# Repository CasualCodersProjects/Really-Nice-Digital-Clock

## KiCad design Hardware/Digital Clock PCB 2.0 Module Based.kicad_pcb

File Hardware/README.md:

# Digital Clock Hardware

## Notice:
There is a hardware change between the 8 clocks sold on Tindie and these. The original production clocks from tindie are:  
- Missing a copper trace between the 3v3 line and the 3v3 output of the LDO. This is corrected with a hand-assembled solder bridge.  
- The I2C lines are shifted right by one pin. The Tindie version uses GPIO 21 for SDA and GPIO 33 for SCL.  
- The Tindie clocks have a manually soldered bodge to move one of the binary coded digits off GPIO 46, which is an input only strapping pin.

## Description
This is an internet connected Clock which synchronizes with NTP servers to perpetually serve an accurate time. It is unable to keep very good time by itself. As such, it requires a stable, consistent network connection to show reliable time. With that, it should always be accurate within a second or so. To improve accuracy, you could modify the firmware to check every hour or half hour instead of once per day.  

It's built using BCD Decoders and 1.5" Seven segment displays for a nice clean look. It also utilizes an ambient light sensor to automatically brighten and dim to match the room light.  

This clock serves it's own webpage for configuration. Upon first boot, it activates an access point ssid `NiceClock`, password `MinesBigger`. Connect to the default gateway `192.168.4.1` to configure the clock and provide network credentials. Once credentials are provided, it should instantly connect and acquire the network time.  
To view the device's IP address, press the boot button on the rear.

## Hacking
This device openly exposes both a TTL UART and JTAG port on the rear of te board, near the ESP Module. You can also use the USB Port to program and upload code. While holding the boot button, then press reset. This enters the ESP32 into bootloader mode, and allows you to re-flash new firmware or filesystem to the device.

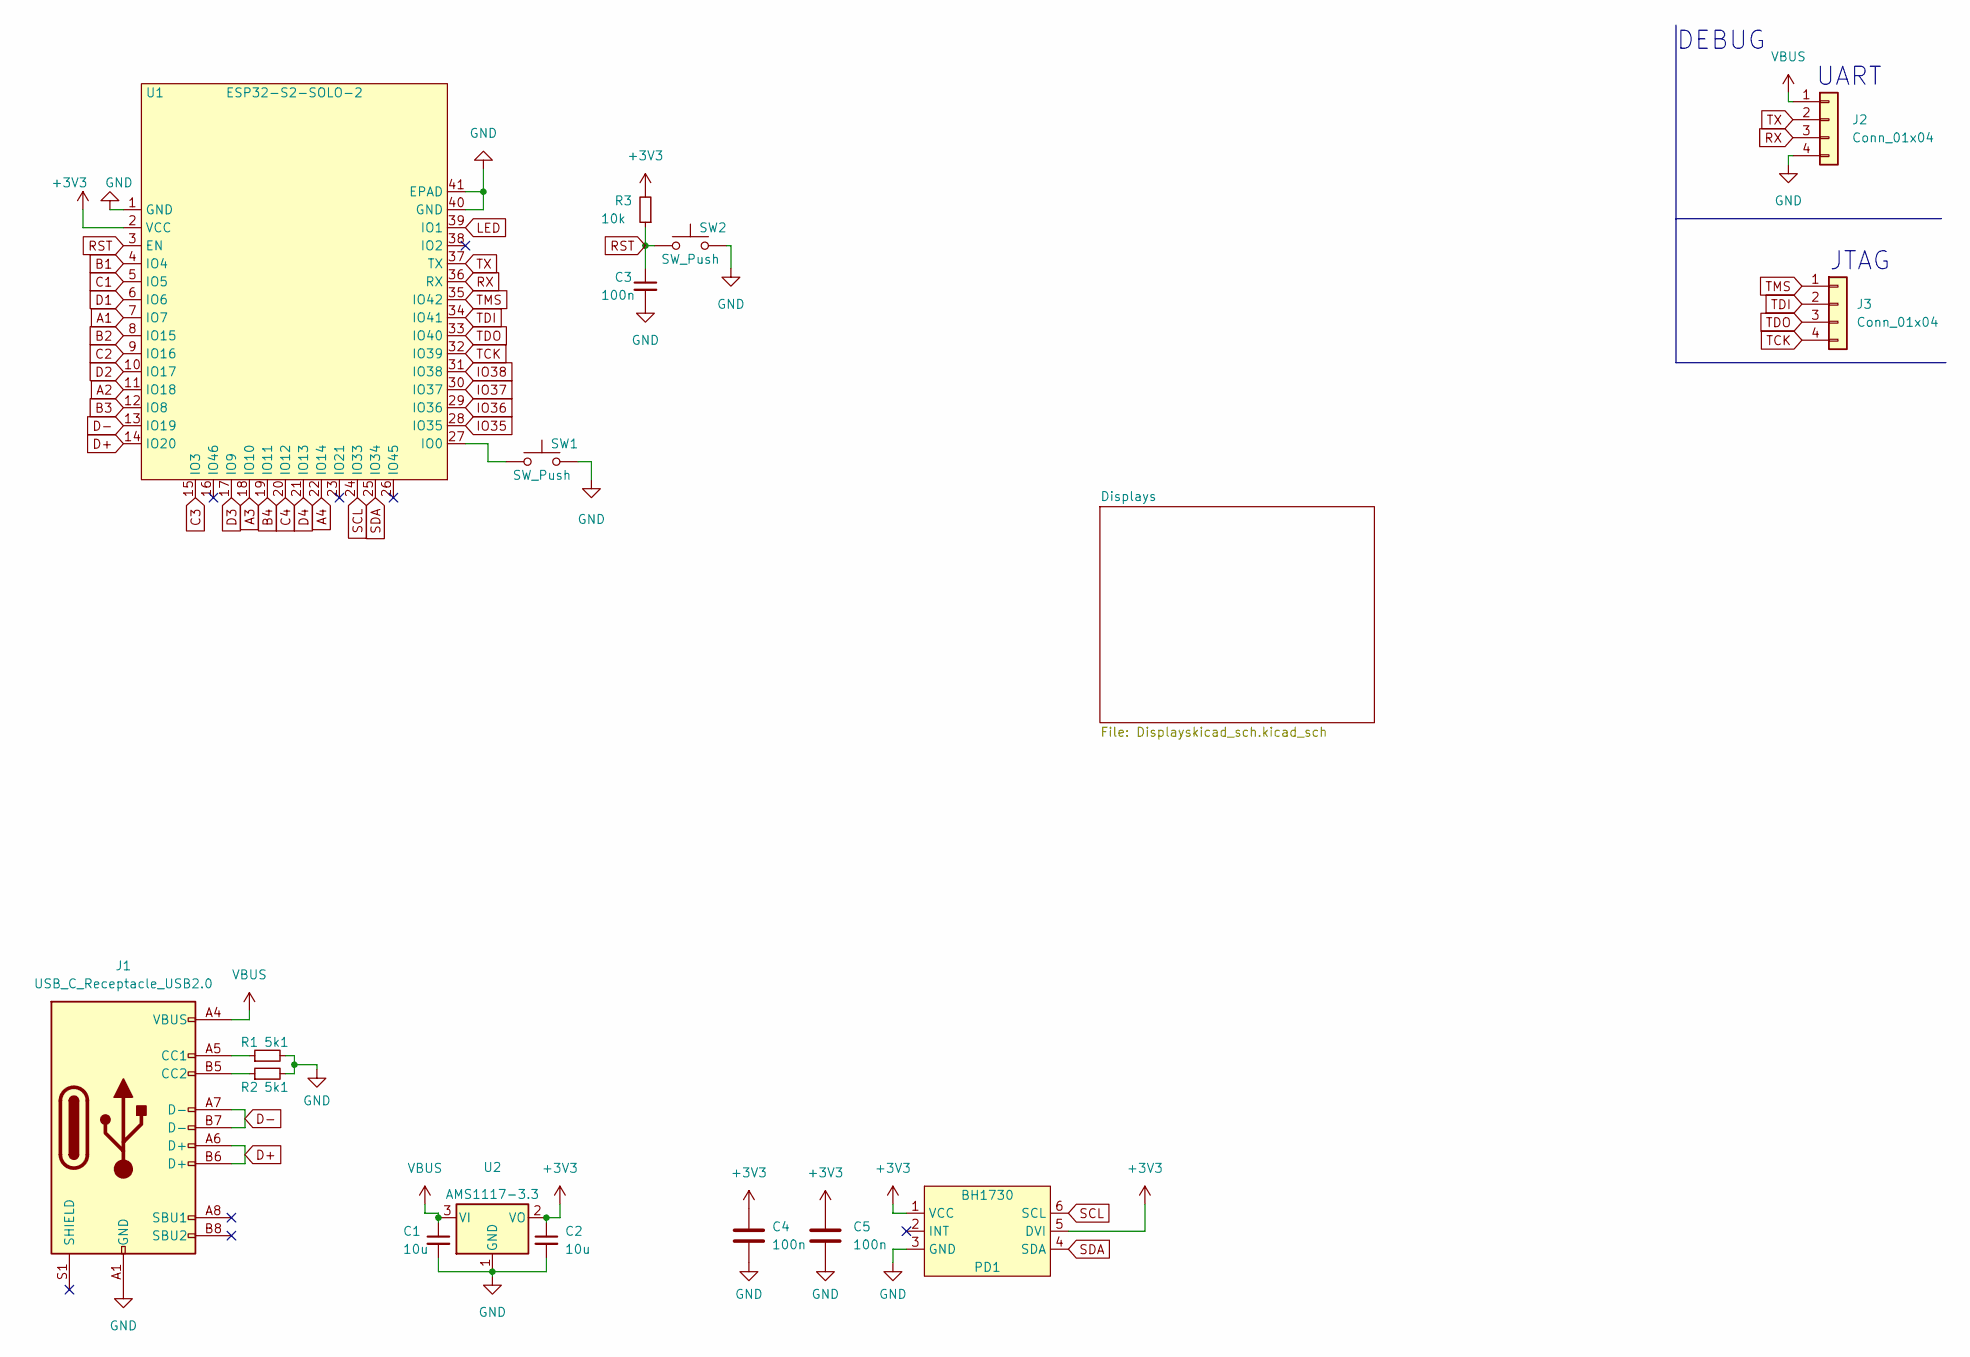
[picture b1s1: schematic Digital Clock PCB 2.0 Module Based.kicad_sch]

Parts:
C1, C2: 10u; C_0805_2012Metric
C3, C4, C5: 100n; C_0603_1608Metric
J1: USB_C_Receptacle_USB2.0; USB_C_Receptacle_HRO_TYPE-C-31-M-12
J2, J3: Conn_01x04; PinHeader_1x04_P2.54mm_Vertical
PD1: BH1730; WSOF6
R1, R2: 5k1; R_0603_1608Metric
R3: 10k; R_0603_1608Metric
SW1, SW2: SW_Push; 5.2mm_Tactile_Push_Button
U1: ESP32-S2-SOLO-2; ESP32-S3-WROOM-1
U2: AMS1117-3.3; SOT-223-3_TabPin2

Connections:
+3V3: C2.1, C4.1, C5.1, PD1.1 (VCC), PD1.5 (DVI), R3.2, U1.2 (VCC), U2.2 (VO); also elsewhere on the board
A1: U1.7 (IO7); also elsewhere on the board
A2: U1.11 (IO18); also elsewhere on the board
A3: U1.18 (IO10); also elsewhere on the board
A4: U1.22 (IO14); also elsewhere on the board
B1: U1.4 (IO4); also elsewhere on the board
B2: U1.8 (IO15); also elsewhere on the board
B3: U1.12 (IO8); also elsewhere on the board
B4: U1.19 (IO11); also elsewhere on the board
C1: U1.5 (IO5); also elsewhere on the board
C2: U1.9 (IO16); also elsewhere on the board
C3: U1.15 (IO3); also elsewhere on the board
C4: U1.20 (IO12); also elsewhere on the board
D1: U1.6 (IO6); also elsewhere on the board
D2: U1.10 (IO17); also elsewhere on the board
D3: U1.17 (IO9); also elsewhere on the board
D4: U1.21 (IO13); also elsewhere on the board
D+: J1.A6 (D+), J1.B6 (D+), U1.14 (IO20)
D-: J1.A7 (D-), J1.B7 (D-), U1.13 (IO19)
GND: C1.2, C2.2, C3.2, C4.2, C5.2, J1.A1 (GND), J1.A12 (GND), J1.B1 (GND), J1.B12 (GND), J2.4, PD1.3 (GND), R1.2, R2.2, SW1.2, SW2.2, U1.1 (GND), U1.40 (GND), U1.41 (EPAD), U2.1 (GND); also elsewhere on the board
IO35: U1.28 (IO35); also elsewhere on the board
IO36: U1.29 (IO36); also elsewhere on the board
IO37: U1.30 (IO37); also elsewhere on the board
IO38: U1.31 (IO38); also elsewhere on the board
LED: U1.39 (IO1); also elsewhere on the board
unnamed: J1.A5 (CC1), R1.1
unnamed: J1.B5 (CC2), R2.1
unnamed: SW1.1, U1.27 (IO0)
RST: C3.1, R3.1, SW2.1, U1.3 (EN)
RX: J2.3, U1.36 (RX)
SCL: PD1.6 (SCL), U1.24 (IO33)
SDA: PD1.4 (SDA), U1.25 (IO34)
TCK: J3.4, U1.32 (IO39)
TDI: J3.2, U1.34 (IO41)
TDO: J3.3, U1.33 (IO40)
TMS: J3.1, U1.35 (IO42)
TX: J2.2, U1.37 (TX)
VBUS: C1.1, J1.A4 (VBUS), J1.A9 (VBUS), J1.B4 (VBUS), J1.B9 (VBUS), J2.1, U2.3 (VI); also elsewhere on the board

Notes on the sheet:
DEBUG
UART
JTAG

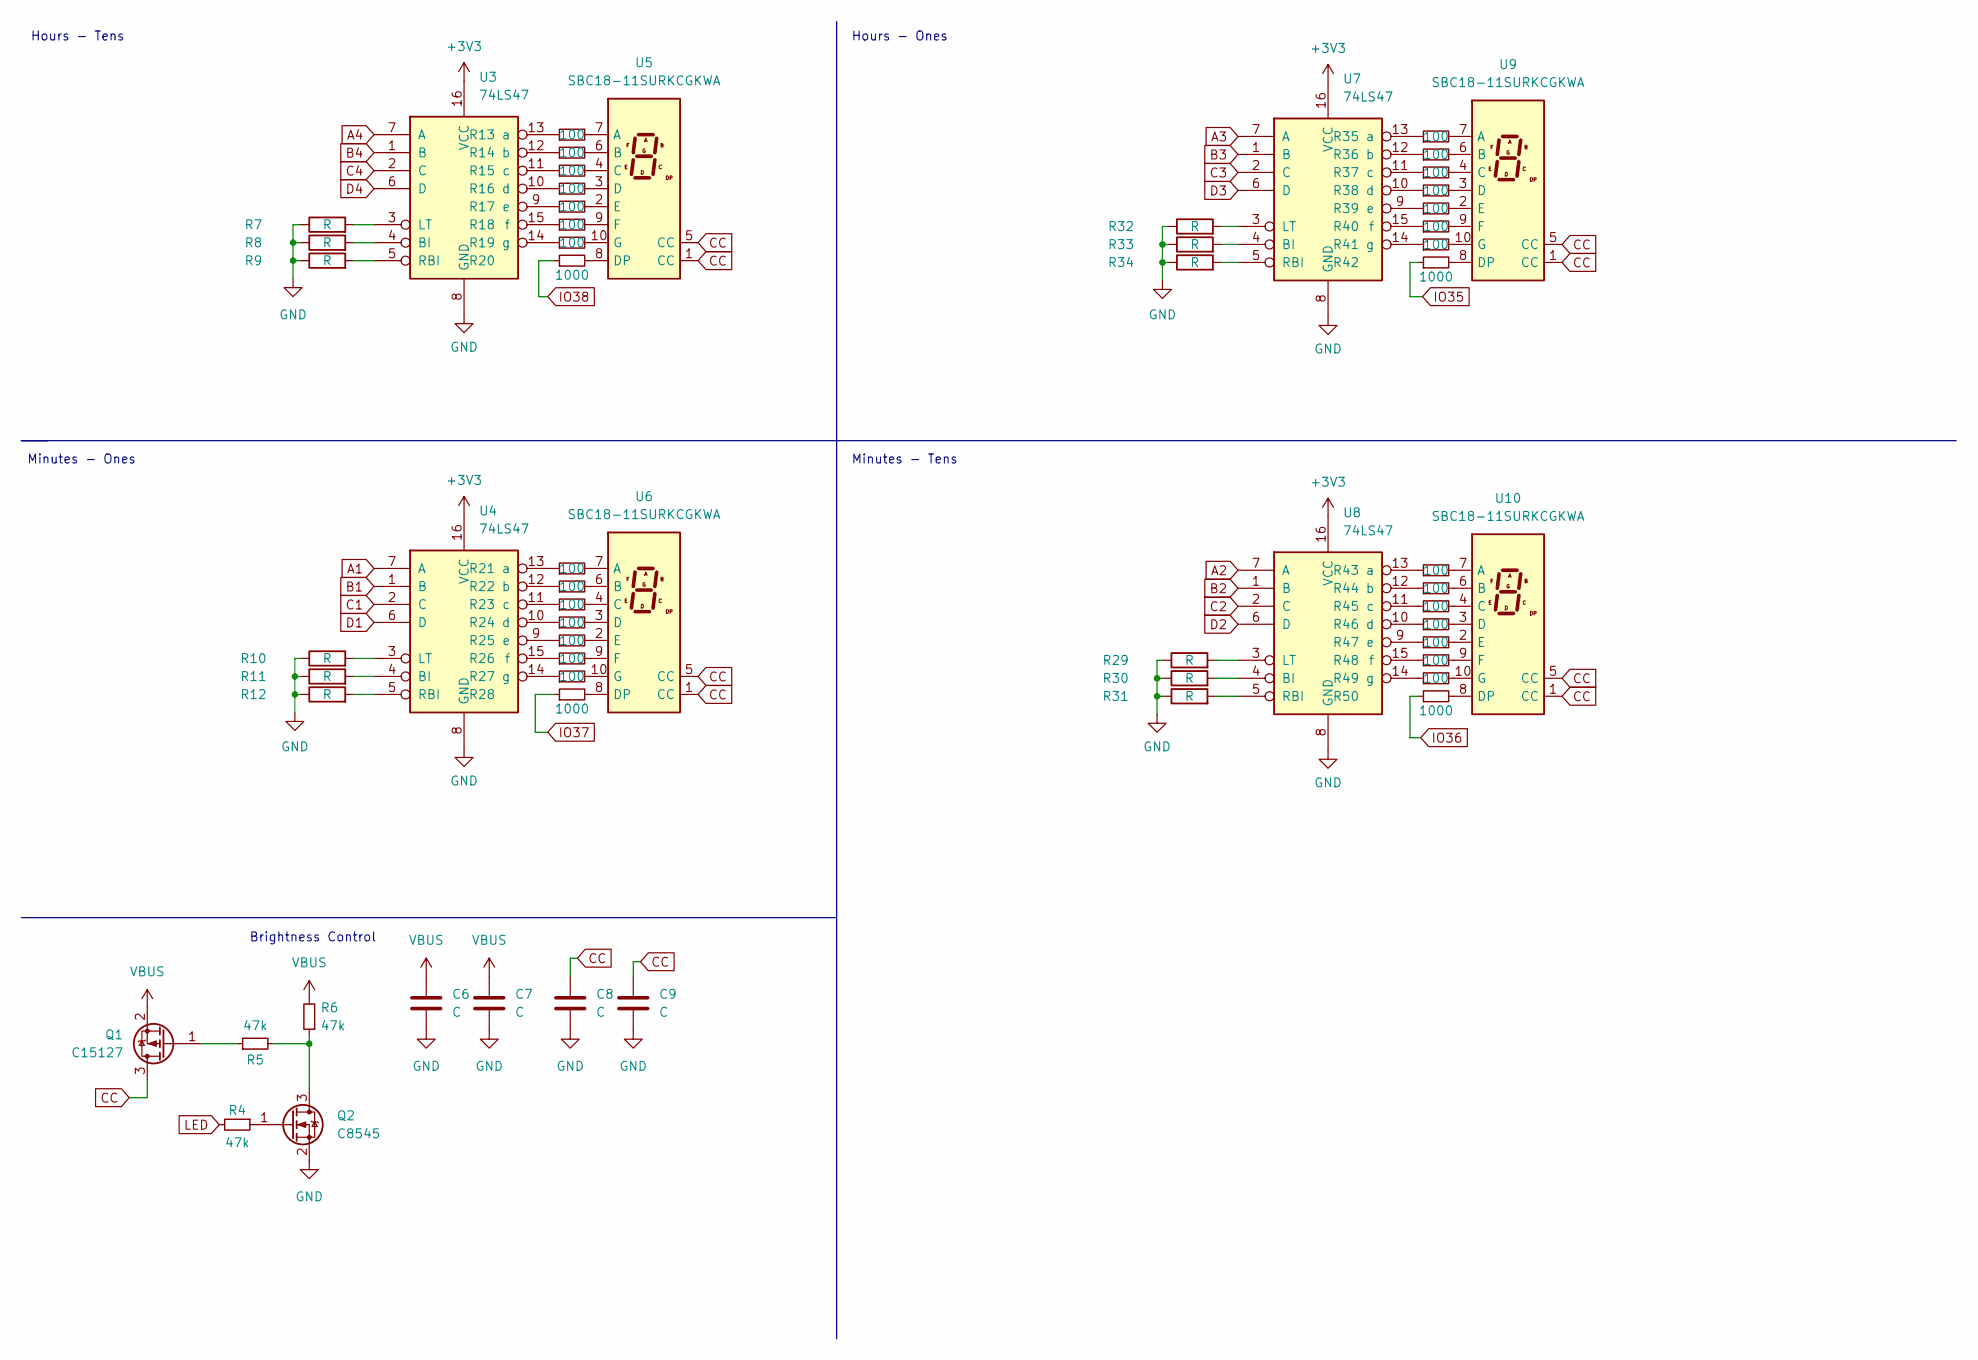
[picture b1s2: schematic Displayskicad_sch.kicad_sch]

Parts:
C6, C7, C8, C9: C; C_0805_2012Metric
Q1: C15127; SOT-23
Q2: C8545; SOT-23
R4, R5, R6: 47k; R_0805_2012Metric
R7, R8, R9, R10, R11, R12, R29, R30, R31, R32, R33, R34: R; R_0603_1608Metric
R13, R14, R15, R16, R17, R18, R19, R21, R22, R23, R24, R25, R26, R27, R35, R36, R37, R38, R39, R40, R41, R43, R44, R45, R46, R47, R48, R49: 100; R_0805_2012Metric
R20, R28, R42, R50: 1000; R_0805_2012Metric
U3, U4, U7, U8: 74LS47; SOIC-16_4.55x10.3mm_P1.27mm
U5, U6, U9, U10: SBC18-11SURKCGKWA; Segment_Display_1-5_inch

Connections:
+3V3: U3.16 (VCC), U4.16 (VCC), U7.16 (VCC), U8.16 (VCC); also elsewhere on the board
A1: U4.7 (A); also elsewhere on the board
A2: U8.7 (A); also elsewhere on the board
A3: U7.7 (A); also elsewhere on the board
A4: U3.7 (A); also elsewhere on the board
B1: U4.1 (B); also elsewhere on the board
B2: U8.1 (B); also elsewhere on the board
B3: U7.1 (B); also elsewhere on the board
B4: U3.1 (B); also elsewhere on the board
C1: U4.2 (C); also elsewhere on the board
C2: U8.2 (C); also elsewhere on the board
C3: U7.2 (C); also elsewhere on the board
C4: U3.2 (C); also elsewhere on the board
CC: C8.1, C9.1, Q1.3 (D), U5.1 (CC), U5.5 (CC), U6.1 (CC), U6.5 (CC), U9.1 (CC), U9.5 (CC), U10.1 (CC), U10.5 (CC)
D1: U4.6 (D); also elsewhere on the board
D2: U8.6 (D); also elsewhere on the board
D3: U7.6 (D); also elsewhere on the board
D4: U3.6 (D); also elsewhere on the board
GND: C6.2, C7.2, C8.2, C9.2, Q2.2 (S), R7.1, R8.1, R9.1, R10.1, R11.1, R12.1, R29.1, R30.1, R31.1, R32.1, R33.1, R34.1, U3.8 (GND), U4.8 (GND), U7.8 (GND), U8.8 (GND); also elsewhere on the board
IO35: R42.1; also elsewhere on the board
IO36: R50.1; also elsewhere on the board
IO37: R28.1; also elsewhere on the board
IO38: R20.1; also elsewhere on the board
LED: R4.2; also elsewhere on the board
unnamed: Q1.1 (G), R5.1
unnamed: Q2.3 (D), R5.2, R6.1
unnamed: Q2.1 (G), R4.1
unnamed: R8.2, U3.4 (BI)
unnamed: R7.2, U3.3 (LT)
unnamed: R9.2, U3.5 (RBI)
unnamed: R13.1, U3.13 (a)
unnamed: R14.1, U3.12 (b)
unnamed: R15.1, U3.11 (c)
unnamed: R16.1, U3.10 (d)
unnamed: R17.1, U3.9 (e)
unnamed: R18.1, U3.15 (f)
unnamed: R19.1, U3.14 (g)
unnamed: R11.2, U4.4 (BI)
unnamed: R10.2, U4.3 (LT)
unnamed: R12.2, U4.5 (RBI)
unnamed: R21.1, U4.13 (a)
unnamed: R22.1, U4.12 (b)
unnamed: R23.1, U4.11 (c)
unnamed: R24.1, U4.10 (d)
unnamed: R25.1, U4.9 (e)
unnamed: R26.1, U4.15 (f)
unnamed: R27.1, U4.14 (g)
unnamed: R13.2, U5.7 (A)
unnamed: R14.2, U5.6 (B)
unnamed: R15.2, U5.4 (C)
unnamed: R16.2, U5.3 (D)
unnamed: R20.2, U5.8 (DP)
unnamed: R17.2, U5.2 (E)
unnamed: R18.2, U5.9 (F)
unnamed: R19.2, U5.10 (G)
unnamed: R21.2, U6.7 (A)
unnamed: R22.2, U6.6 (B)
unnamed: R23.2, U6.4 (C)
unnamed: R24.2, U6.3 (D)
unnamed: R28.2, U6.8 (DP)
unnamed: R25.2, U6.2 (E)
unnamed: R26.2, U6.9 (F)
unnamed: R27.2, U6.10 (G)
unnamed: R33.2, U7.4 (BI)
unnamed: R32.2, U7.3 (LT)
unnamed: R34.2, U7.5 (RBI)
unnamed: R35.1, U7.13 (a)
unnamed: R36.1, U7.12 (b)
unnamed: R37.1, U7.11 (c)
unnamed: R38.1, U7.10 (d)
unnamed: R39.1, U7.9 (e)
unnamed: R40.1, U7.15 (f)
unnamed: R41.1, U7.14 (g)
unnamed: R30.2, U8.4 (BI)
unnamed: R29.2, U8.3 (LT)
unnamed: R31.2, U8.5 (RBI)
unnamed: R43.1, U8.13 (a)
unnamed: R44.1, U8.12 (b)
unnamed: R45.1, U8.11 (c)
unnamed: R46.1, U8.10 (d)
unnamed: R47.1, U8.9 (e)
unnamed: R48.1, U8.15 (f)
unnamed: R49.1, U8.14 (g)
unnamed: R35.2, U9.7 (A)
unnamed: R36.2, U9.6 (B)
unnamed: R37.2, U9.4 (C)
unnamed: R38.2, U9.3 (D)
unnamed: R42.2, U9.8 (DP)
unnamed: R39.2, U9.2 (E)
unnamed: R40.2, U9.9 (F)
unnamed: R41.2, U9.10 (G)
unnamed: R43.2, U10.7 (A)
unnamed: R44.2, U10.6 (B)
unnamed: R45.2, U10.4 (C)
unnamed: R46.2, U10.3 (D)
unnamed: R50.2, U10.8 (DP)
unnamed: R47.2, U10.2 (E)
unnamed: R48.2, U10.9 (F)
unnamed: R49.2, U10.10 (G)
VBUS: C6.1, C7.1, Q1.2 (S), R6.2; also elsewhere on the board

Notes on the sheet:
Hours - Tens
Hours - Ones
Minutes - Tens
Brightness Control
Minutes - Ones

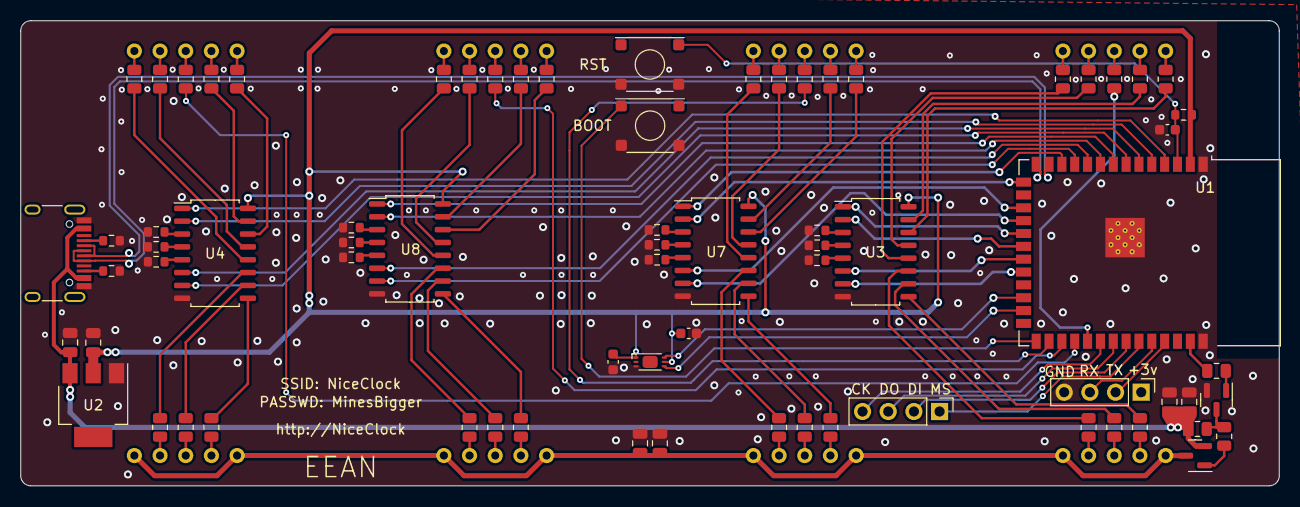
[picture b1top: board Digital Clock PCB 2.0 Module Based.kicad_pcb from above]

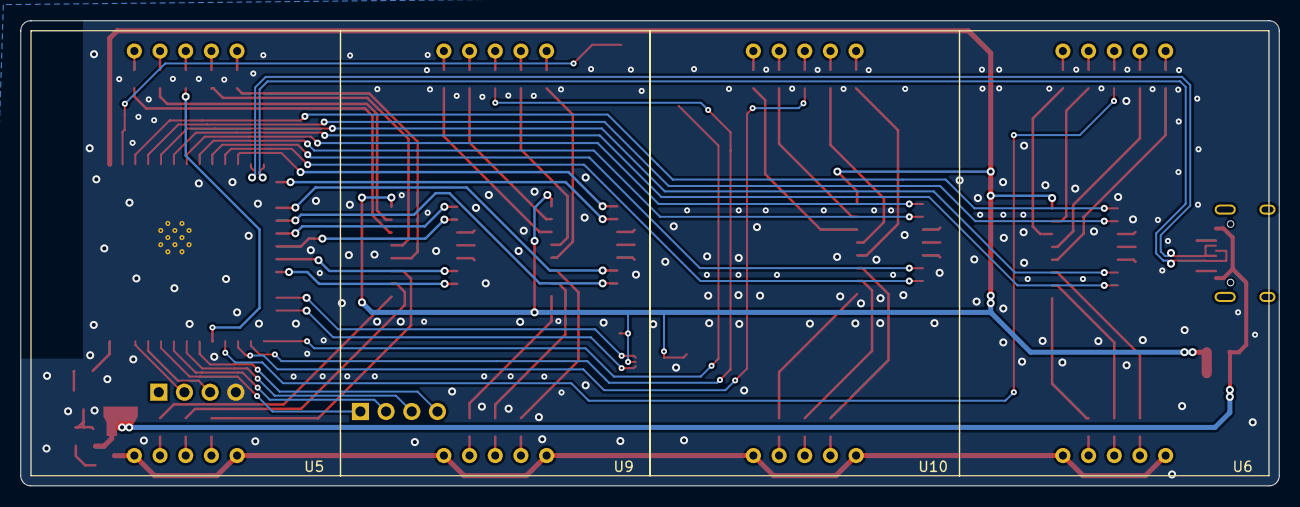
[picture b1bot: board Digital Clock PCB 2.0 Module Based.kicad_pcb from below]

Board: 2 copper layers, 124.5 x 46.0 mm, 77 parts (4 on the bottom side), 114 nets.

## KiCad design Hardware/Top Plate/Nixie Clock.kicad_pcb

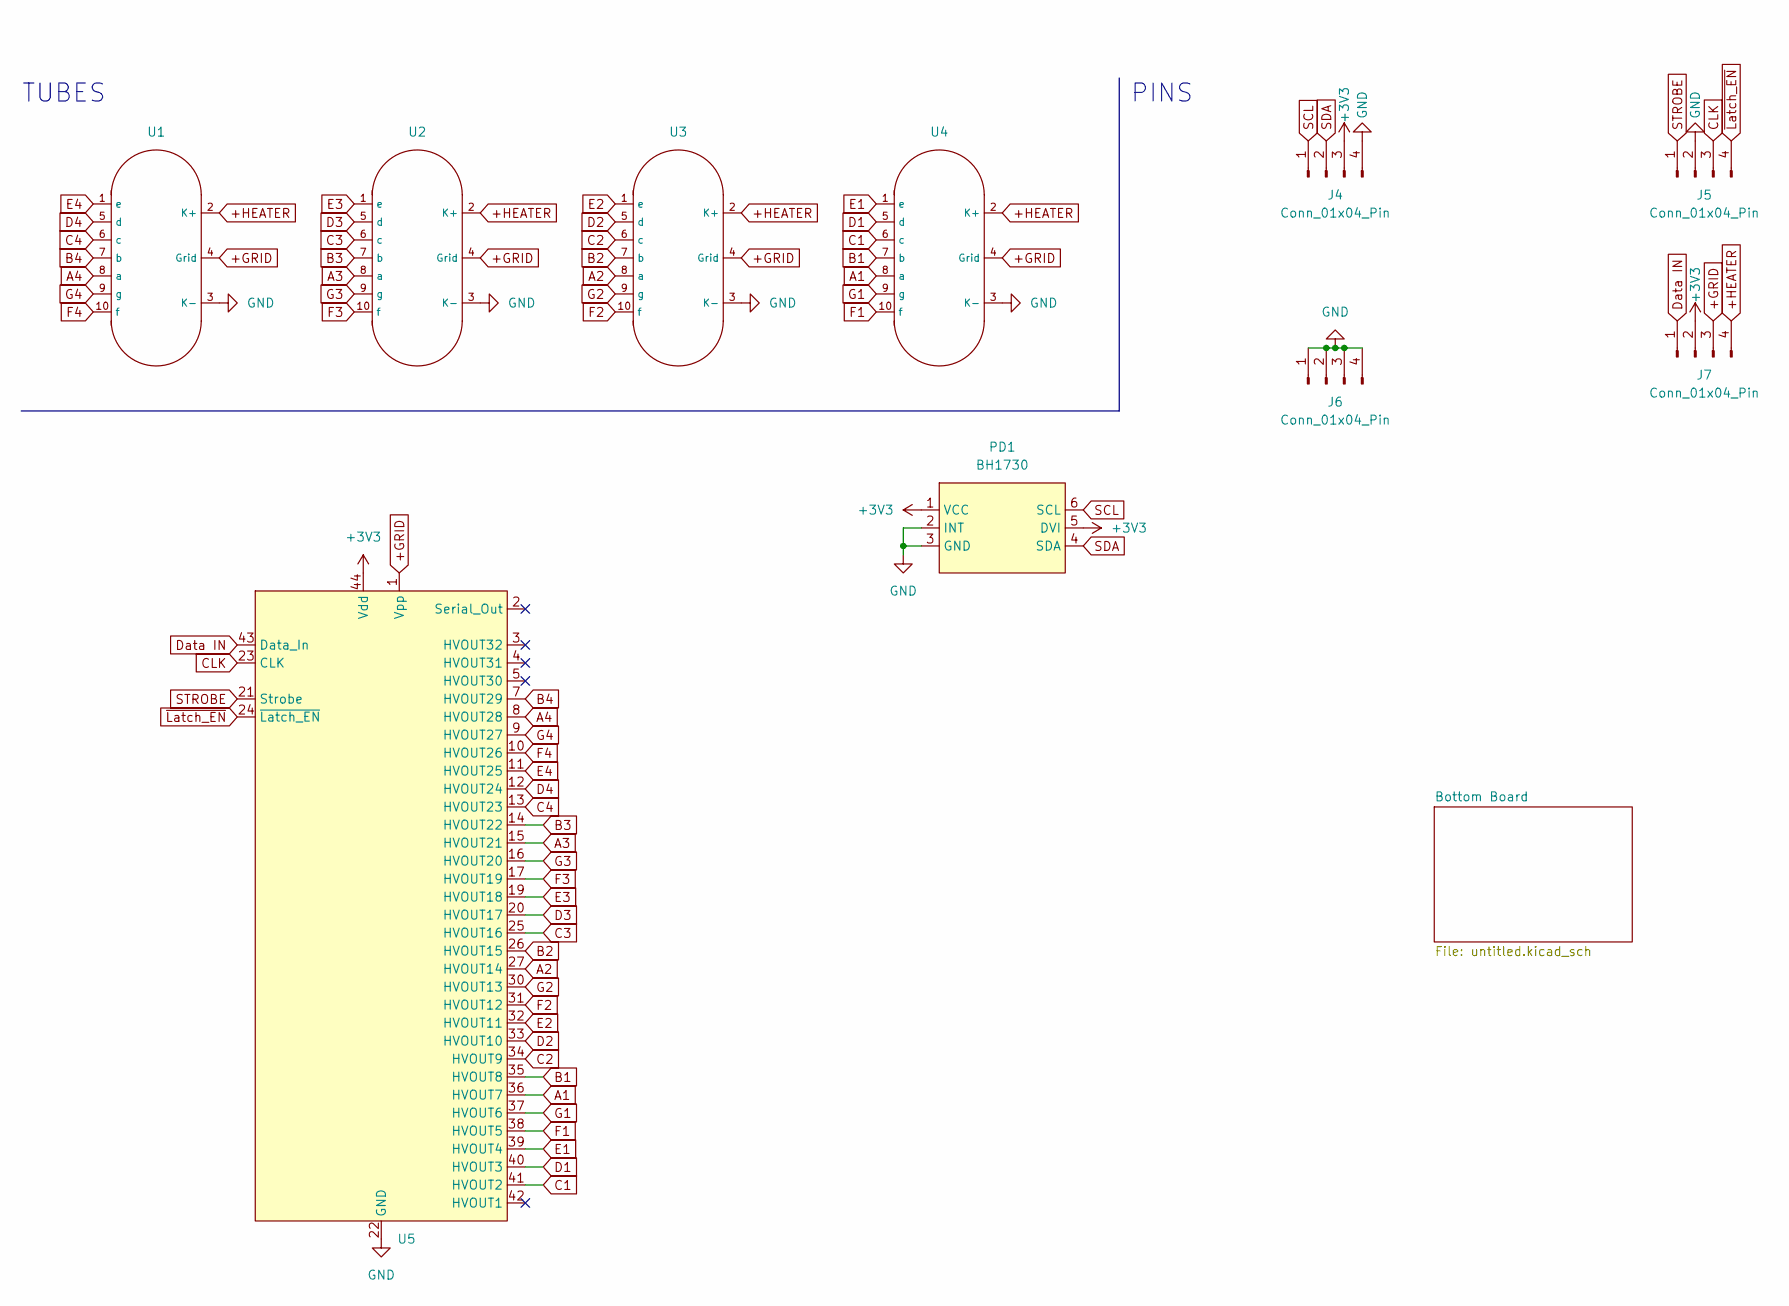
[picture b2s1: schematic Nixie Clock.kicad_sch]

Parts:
J4, J5, J6, J7: Conn_01x04_Pin; PinHeader_1x04_P2.54mm_Vertical_SMD_Pin1Left
PD1: BH1730; WSOF6
U1, U2, U3, U4: IV-12 (From Real Measurements)
U5: PLCC-44

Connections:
+3V3: J4.3, J7.2, PD1.1 (VCC), PD1.5 (DVI), U5.44 (Vdd); also elsewhere on the board
+GRID: J7.3, U1.4 (Grid), U2.4 (Grid), U3.4 (Grid), U4.4 (Grid), U5.1 (Vpp); also elsewhere on the board
+HEATER: J7.4, U1.2 (K+), U2.2 (K+), U3.2 (K+), U4.2 (K+); also elsewhere on the board
A1: U4.8 (a), U5.36 (HVOUT7)
A2: U3.8 (a), U5.27 (HVOUT14)
A3: U2.8 (a), U5.15 (HVOUT21)
A4: U1.8 (a), U5.8 (HVOUT28)
B1: U4.7 (b), U5.35 (HVOUT8)
B2: U3.7 (b), U5.26 (HVOUT15)
B3: U2.7 (b), U5.14 (HVOUT22)
B4: U1.7 (b), U5.7 (HVOUT29)
C1: U4.6 (c), U5.41 (HVOUT2)
C2: U3.6 (c), U5.34 (HVOUT9)
C3: U2.6 (c), U5.25 (HVOUT16)
C4: U1.6 (c), U5.13 (HVOUT23)
CLK: J5.3, U5.23 (CLK); also elsewhere on the board
D1: U4.5 (d), U5.40 (HVOUT3)
D2: U3.5 (d), U5.33 (HVOUT10)
D3: U2.5 (d), U5.20 (HVOUT17)
D4: U1.5 (d), U5.12 (HVOUT24)
Data IN: J7.1, U5.43 (Data_In); also elsewhere on the board
E1: U4.1 (e), U5.39 (HVOUT4)
E2: U3.1 (e), U5.32 (HVOUT11)
E3: U2.1 (e), U5.19 (HVOUT18)
E4: U1.1 (e), U5.11 (HVOUT25)
F1: U4.10 (f), U5.38 (HVOUT5)
F2: U3.10 (f), U5.31 (HVOUT12)
F3: U2.10 (f), U5.17 (HVOUT19)
F4: U1.10 (f), U5.10 (HVOUT26)
G1: U4.9 (g), U5.37 (HVOUT6)
G2: U3.9 (g), U5.30 (HVOUT13)
G3: U2.9 (g), U5.16 (HVOUT20)
G4: U1.9 (g), U5.9 (HVOUT27)
GND: J4.4, J5.2, J6.1, J6.2, J6.3, J6.4, PD1.2 (INT), PD1.3 (GND), U1.3 (K-), U2.3 (K-), U3.3 (K-), U4.3 (K-), U5.22 (GND); also elsewhere on the board
SCL: J4.1, PD1.6 (SCL); also elsewhere on the board
SDA: J4.2, PD1.4 (SDA); also elsewhere on the board
STROBE: J5.1, U5.21 (Strobe); also elsewhere on the board
~Latch_EN: J5.4, U5.24 (~Latch_EN); also elsewhere on the board

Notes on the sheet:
TUBES
PINS

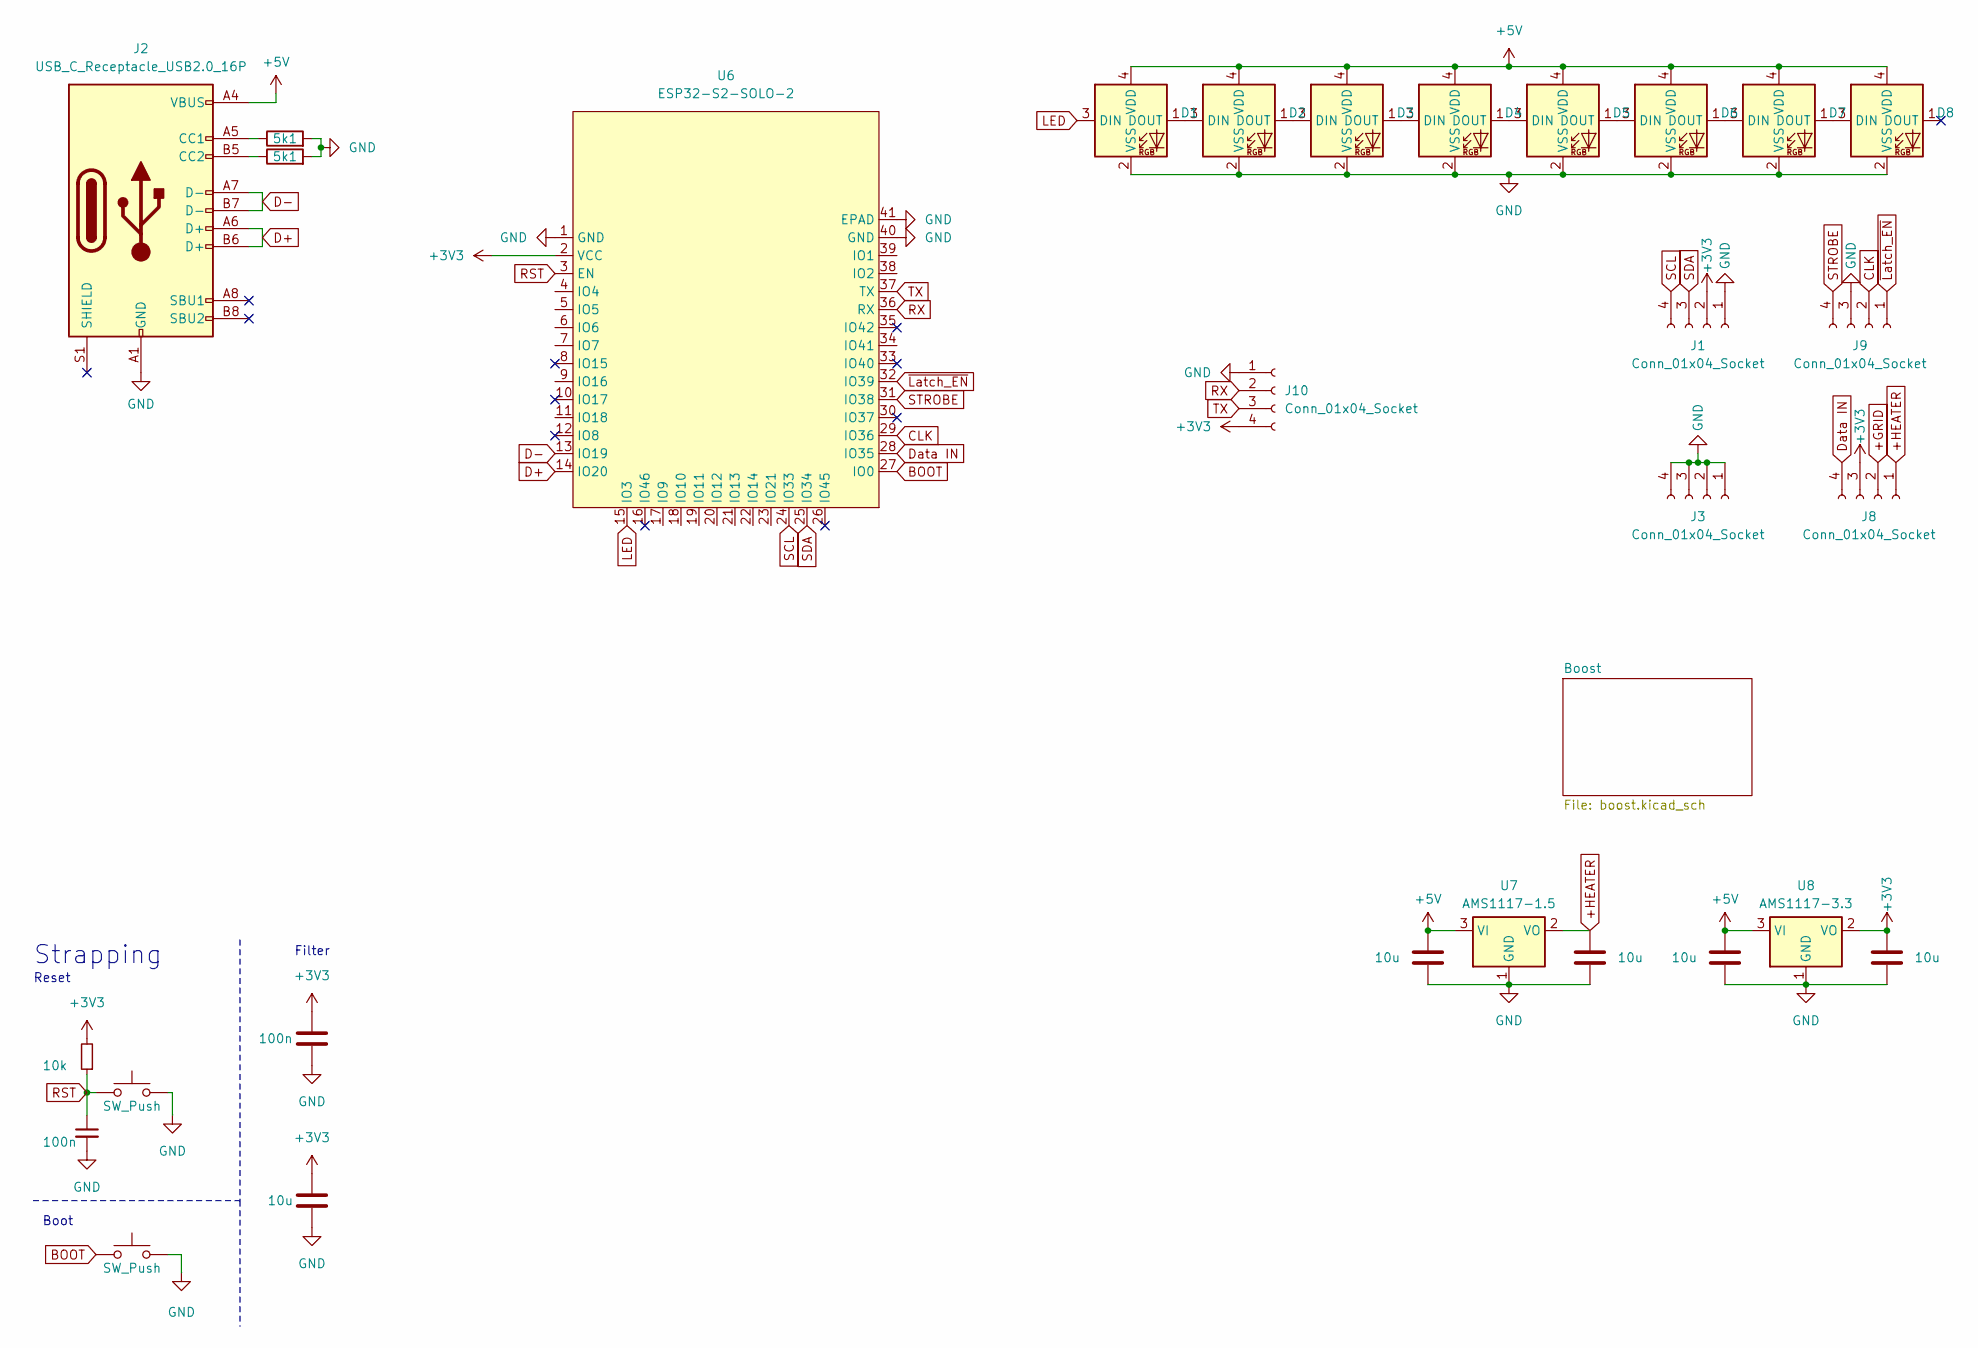
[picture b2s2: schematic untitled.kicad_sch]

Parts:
C1, C2, C3, C4, C15: 10u; C_0603_1608Metric
C13, C14: 100n; C_0402_1005Metric
D1, D2, D3, D4, D5, D6, D7, D8: LED_WS2812B-2020_PLCC4_2.0x2.0mm
J1, J3, J8, J9, J10: Conn_01x04_Socket; PinHeader_1x04_P2.54mm_Vertical
J2: USB_C_Receptacle_USB2.0_16P; USB_C_Receptacle_HRO_TYPE-C-31-M-12
R1, R2: 5k1; R_0603_1608Metric
R7: 10k; R_0402_1005Metric
RST1: SW_Push; SW_SPST_SKQG_WithStem
SW2: SW_Push; SW_SPST_SKQG_WithStem
U6: ESP32-S2-SOLO-2; ESP32-S3-WROOM-1
U7: AMS1117-1.5; SOT-223-3_TabPin2
U8: AMS1117-3.3; SOT-223-3_TabPin2

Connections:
+3V3: C4.1, C13.1, C15.1, J1.2, J8.3, J10.4, R7.2, U6.2 (VCC), U8.2 (VO); also elsewhere on the board
+5V: C1.1, C3.1, D1.4 (VDD), D2.4 (VDD), D3.4 (VDD), D4.4 (VDD), D5.4 (VDD), D6.4 (VDD), D7.4 (VDD), D8.4 (VDD), J2.A4 (VBUS), J2.A9 (VBUS), J2.B4 (VBUS), J2.B9 (VBUS), U7.3 (VI), U8.3 (VI); also elsewhere on the board
+GRID: J8.2; also elsewhere on the board
+HEATER: C2.1, J8.1, U7.2 (VO); also elsewhere on the board
BOOT: SW2.1, U6.27 (IO0); also elsewhere on the board
CLK: J9.2, U6.29 (IO36); also elsewhere on the board
D+: J2.A6 (D+), J2.B6 (D+), U6.14 (IO20)
D-: J2.A7 (D-), J2.B7 (D-), U6.13 (IO19)
Data IN: J8.4, U6.28 (IO35); also elsewhere on the board
GND: C1.2, C2.2, C3.2, C4.2, C13.2, C14.2, C15.2, D1.2 (VSS), D2.2 (VSS), D3.2 (VSS), D4.2 (VSS), D5.2 (VSS), D6.2 (VSS), D7.2 (VSS), D8.2 (VSS), J1.1, J2.A1 (GND), J2.A12 (GND), J2.B1 (GND), J2.B12 (GND), J3.1, J3.2, J3.3, J3.4, J9.3, J10.1, R1.2, R2.2, RST1.2, SW2.2, U6.1 (GND), U6.40 (GND), U6.41 (EPAD), U7.1 (GND), U8.1 (GND); also elsewhere on the board
LED: D1.3 (DIN), U6.15 (IO3)
unnamed: D1.1 (DOUT), D2.3 (DIN)
unnamed: D2.1 (DOUT), D3.3 (DIN)
unnamed: D3.1 (DOUT), D4.3 (DIN)
unnamed: D4.1 (DOUT), D5.3 (DIN)
unnamed: D5.1 (DOUT), D6.3 (DIN)
unnamed: D6.1 (DOUT), D7.3 (DIN)
unnamed: D7.1 (DOUT), D8.3 (DIN)
unnamed: J2.A5 (CC1), R1.1
unnamed: J2.B5 (CC2), R2.1
RST: C14.1, R7.1, RST1.1, U6.3 (EN); also elsewhere on the board
RX: J10.2, U6.36 (RX)
SCL: J1.4, U6.24 (IO33); also elsewhere on the board
SDA: J1.3, U6.25 (IO34); also elsewhere on the board
STROBE: J9.4, U6.31 (IO38); also elsewhere on the board
TX: J10.3, U6.37 (TX)
~Latch_EN: J9.1, U6.32 (IO39); also elsewhere on the board

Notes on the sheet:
Reset
Filter
Strapping
Boot

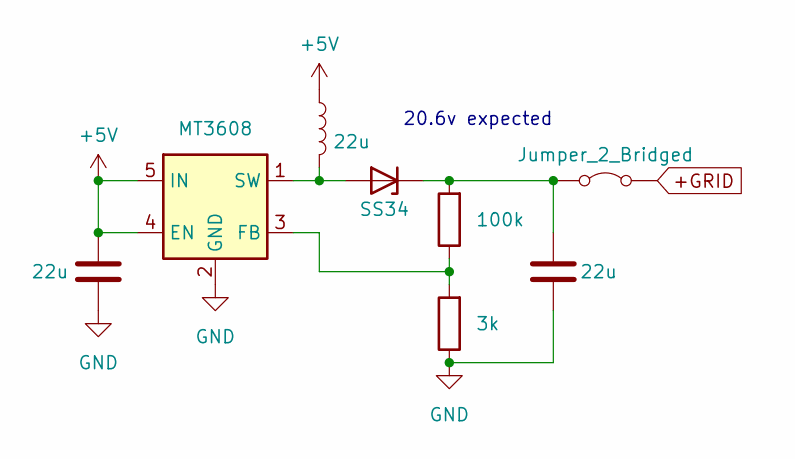
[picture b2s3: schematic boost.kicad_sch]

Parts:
C5, C6: 22u; C_1206_3216Metric
D9: SS34; D_SMA
JP1: Jumper_2_Bridged; R_0402_1005Metric_Pad0.72x0.64mm_HandSolder
L1: 22u; L_7.3x7.3_H3.5
R3: 100k; R_0402_1005Metric
R4: 3k; R_0402_1005Metric
U9: MT3608; SOT-23-6

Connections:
+5V: C5.1, L1.1, U9.4 (EN), U9.5 (IN); also elsewhere on the board
+GRID: JP1.2 (B); also elsewhere on the board
GND: C5.2, C6.2, R4.1, U9.2 (GND); also elsewhere on the board
unnamed: D9.2 (A), L1.2, U9.1 (SW)
unnamed: C6.1, D9.1 (K), JP1.1 (A), R3.2
unnamed: R3.1, R4.2, U9.3 (FB)

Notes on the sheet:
20.6v expected

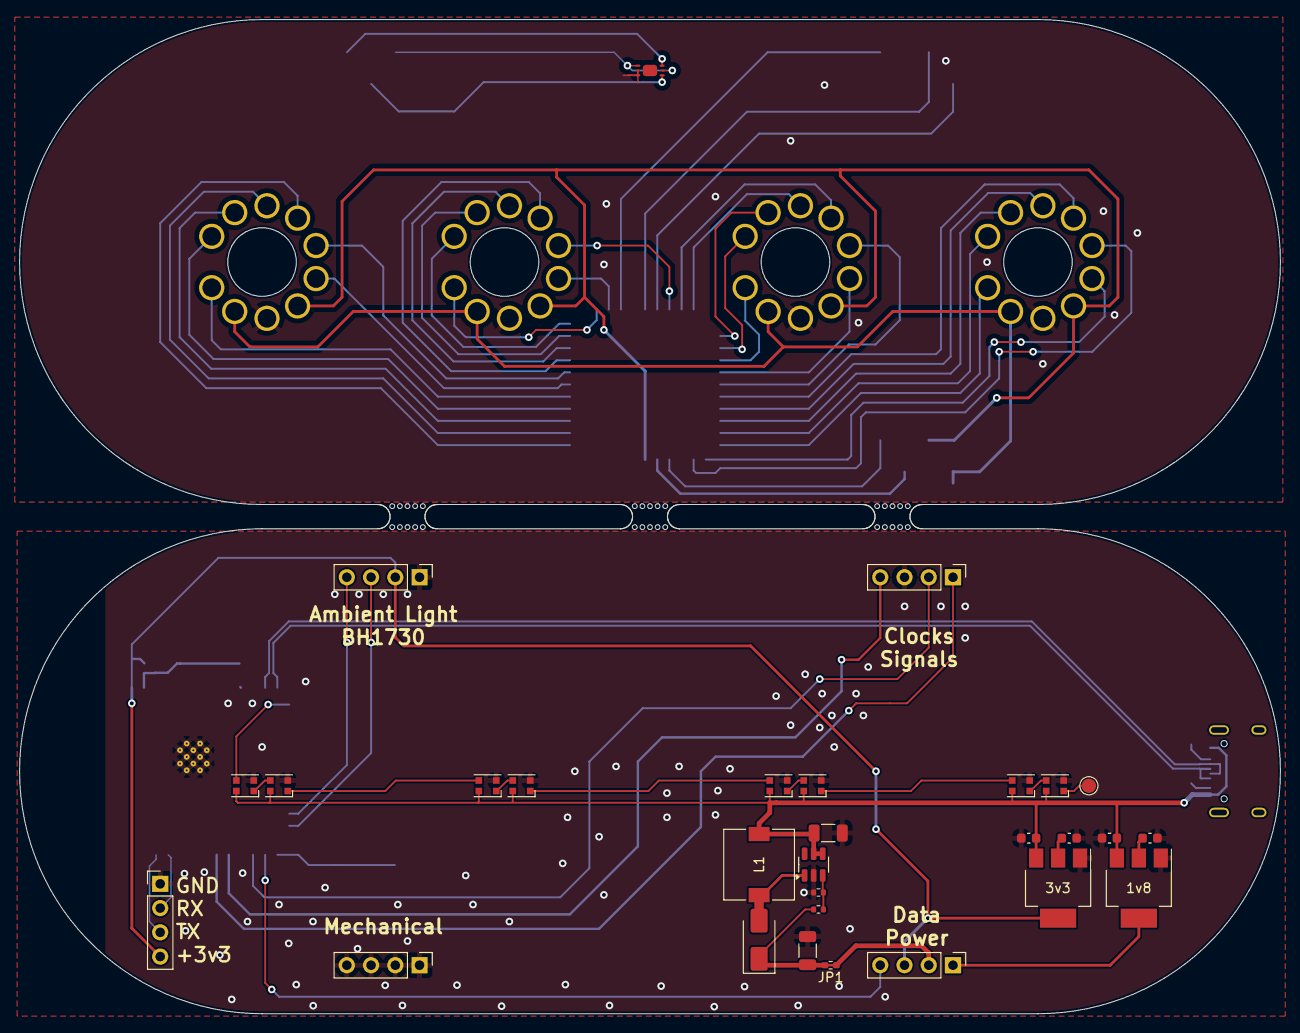
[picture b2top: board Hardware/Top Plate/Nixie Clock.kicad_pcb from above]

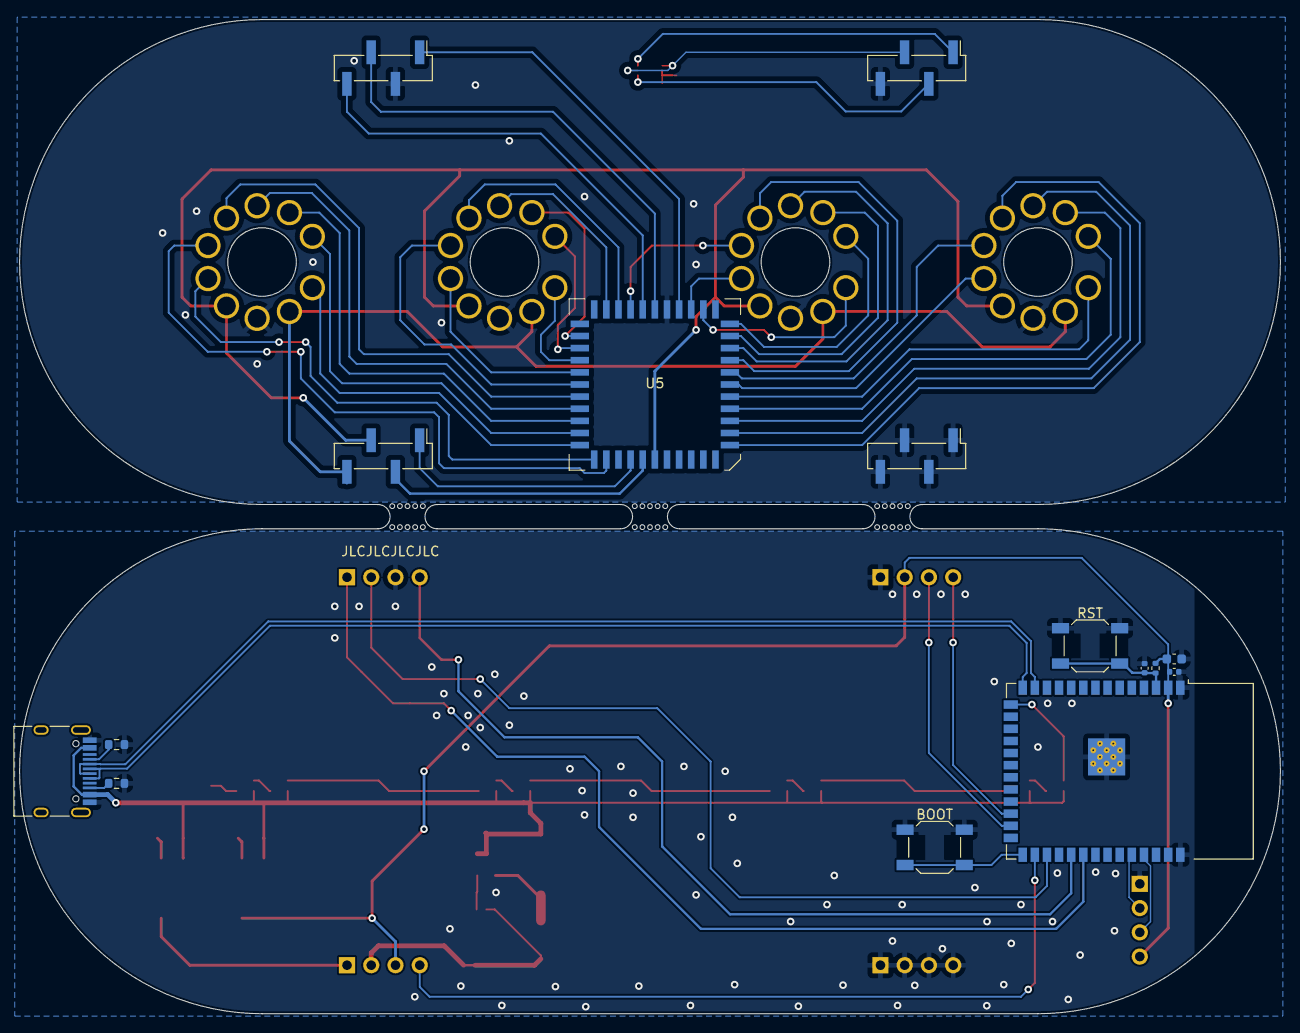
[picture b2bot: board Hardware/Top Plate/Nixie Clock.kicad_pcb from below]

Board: 2 copper layers, 132.1 x 104.1 mm, 50 parts (15 on the bottom side), 58 nets.

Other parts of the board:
1v8: AMS1117-1.5; SOT-223-3_TabPin2
3v3: AMS1117-3.3; SOT-223-3_TabPin2
BOOT: SW_Push; SW_SPST_SKQG_WithStem
RST: SW_Push; SW_SPST_SKQG_WithStem
mouse-bite-2.54mm-slot, mouse-bite-2.54mm-slot#2, mouse-bite-2.54mm-slot#3: VAL**; mouse-bite-2.54mm-slot

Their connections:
+3V3: 3v3.2 (VO); also elsewhere on the board
+5V: 1v8.3 (VI), 3v3.3 (VI); also elsewhere on the board
+HEATER: 1v8.2 (VO); also elsewhere on the board
BOOT: BOOT.1; also elsewhere on the board
GND: 1v8.1 (GND), 3v3.1 (GND), BOOT.2, RST.2; also elsewhere on the board
RST: RST.1; also elsewhere on the board
